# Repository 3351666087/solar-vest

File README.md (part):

<div align="center">

# Solar Vest

**A self-powered, solar-harvesting wearable for ECG research**<br>
**一件为心电研究而做的太阳能自供电可穿戴背心**

**[English](#english) | [中文](#中文)**

</div>

---

## English

### What it is

Solar Vest is a research platform that answers one question:

> **Can a body-worn 6 V / 6 W solar panel keep a Bluetooth ECG acquisition unit running, and does solar powering change the ECG signal compared with an identical battery-powered control recorded on the same subject at the same time?**

A rigid 6 V / 6 W panel rides on the back of a vest. It charges a 1S Li-ion cell through **PMB-H**, an MPPT charger and power-monitor board of our own design. The battery feeds **BITalino B** (the device under test) through **LIB**, an ideal-diode hold-up board with supercapacitors. **BITalino C** records ECG from mirror-symmetric electrodes on its own battery as the control, and **BITalino A** (HeartBIT) adds ear-lobe PPG. Six INA226 monitors log every energy path, and a XIAO nRF52840 streams the telemetry over BLE to a gateway and on to a remote web console.

The energy budget (see [docs/architecture-v3.md](docs/architecture-v3.md)) says continuous acquisition is only fully self-powered on good days; on a typical day the panel extends runtime by about 76 %, and duty-cycled measurement reaches energy balance.

### System architecture

```mermaid
flowchart LR
    PV["6 V / 6 W solar panel"] --> PMB
    REF["REF1 / REF2 reference cells"] --> PMB

    subgraph PMB["PMB-H (back pod)"]
        direction TB
        CHG["CN3791 MPPT charger<br/>night back-feed cut-off"]
        INA["6 x INA226<br/>PV hi/lo, BAT, LOAD, REF1, REF2"]
        MCU["XIAO nRF52840 Sense<br/>firmware v2"]
        INA -- "I2C" --> MCU
    end

    CHG <--> BAT["1S Li-ion 2500 mAh"]
    PMB -- "VLOAD (LOAD_EN)" --> LIB["LIB (chest pod)<br/>LM66100 ideal diode<br/>+ 2 x 10 F supercaps"]
    LIB --> B["BITalino B<br/>Core BLE, ECG (DUT)"]
    C["BITalino C<br/>Board Kit BLE, ECG<br/>own battery (control)"]
    A["BITalino A<br/>HeartBIT, ear-lobe PPG"]

    MCU -- "BLE telemetry / commands" --> GW["Gateway<br/>Mac (bleak) | ESP32 (MicroPython) | browser relay"]
    GW -- "HTTPS /api/ingest" --> SRV["Console server<br/>console.example.org"]
    SRV --> UI["Web console"]
    B -. "BLE ECG" .-> PHONE["Phone / Mac recording"]
    C -. "BLE ECG" .-> PHONE
    A -. "Classic BT PPG" .-> PHONE
```

### Hardware

| Part | What it is | Where |
|---|---|---|
| **PMB-H** (back pod) | CN3791 MPPT charger (set point 5.93 V), night back-feed cut-off, 6 × INA226 (panel high / indoor range, battery, load, two reference cells), NTC, XIAO nRF52840 Sense logger | [`hardware/pcb/pmbh/`](hardware/pcb/pmbh/) |
| **LIB** (chest pod) | Hold-up board: feeds BITalino Core B through an LM66100 ideal diode; 2 × 10 F supercaps take over if the supply drops | [`hardware/pcb/libb/`](hardware/pcb/libb/) |
| Fabrication outputs | KiCad 10 projects (generated from SKiDL), schematics PDF, Gerbers, JLCPCB BOM + CPL (`*_v3.xlsx` are the ordered files), 3D models, final placement images, rotation audit | [`hardware/pcb/`](hardware/pcb/) |
| Enclosures | 18 printable parts (STEP / STL / 3MF): back pod, chest pod, C case, ear clip, six panel shoes (18–52 mm air gap), REF holders, bench stand, webbing hook | [`hardware/enclosures/`](hardware/enclosures/) (read `README_print-list.txt`) |
| Vest patterns | Shell, lining and accessory patterns: DXF, 1:1 plotter PDF, A4 tiles, body-fitted placement data | [`hardware/vest/`](hardware/vest/) |
| Wiring | 20-wire harness specified pin-to-pin with routed lengths: table (md / csv), system diagram (svg), interactive guide | [`hardware/wiring/`](hardware/wiring/) |
| BITalino A / B / C | A: HeartBIT (Core BT) + ear-lobe PPG · B: Core BLE, solar-powered DUT · C: Board Kit BLE on its own battery (control) | [`docs/bom-and-system-overview.md`](docs/bom-and-system-overview.md) |

### Software

| Component | What it is | Where |
|---|---|---|
| Firmware | Arduino sketch for the XIAO nRF52840: INA226 sampling, MPPT / charge / load control, safety lockouts, BLE GATT telemetry and commands, settings persisted in flash | [`firmware/solarvest_pmb/`](firmware/solarvest_pmb/) |
| Bring-up sketch | Serial-console bench test for PMB-H (toggle every control pin, read every INA226) | [`firmware/pmbh_bringup/`](firmware/pmbh_bringup/), [`tools/serial_bridge.py`](tools/serial_bridge.py) |
| Console server | Python 3.12, standard library only; SQLite storage, session login, device-token ingest, command queue; single-file HTML console with Web Bluetooth relay | [`software/server/`](software/server/) |
| Mac gateway | Python + `bleak`; BLE central → HTTPS, offline buffer, runs unattended under `caffeinate` | [`software/gateway-mac/`](software/gateway-mac/) |
| ESP32 gateway | MicroPython 1.28 port of the same gateway (uses `aioble`) | [`software/gateway-esp32/`](software/gateway-esp32/) |
| Protocol | Interface spec (GATT layout, HTTP API, console UI) and shared decode test vectors | [`software/SPEC.md`](software/SPEC.md), [`software/protocol/vectors.json`](software/protocol/vectors.json) |
| CAD / EDA generators | build123d enclosures, SKiDL / pcbnew board scripts, JLCPCB rotation check, vest patterns, harness, fit checks, ngspice testbenches | [`tools/cad/`](tools/cad/) |

### Repository map

```text
.
├── docs/          Architecture v3 (+ v1/v2 history), v3.1 change list, build & assembly guide,
│                  BOM cross-reference, retrospective, tailoring survey, renders
├── hardware/      PCB projects and fab files, printable enclosures, vest patterns, wiring
├── firmware/      XIAO nRF52840 firmware, bench bring-up sketch, packing check
├── software/      Console server, Mac and ESP32 gateways, protocol spec and test vectors
├── simulation/    ngspice report and figures (MPPT stability, night back-feed, hold-up)
├── explorer/      Interactive 3D explorer (open index.html, works offline)
├── viewer/        Earlier glTF viewer of the full assembly (incl. a body-fitted variant)
├── modeling/      Component models: BITalino Core, panel, supercap, HeartBIT kit, viewer
├── body/          Body reconstruction used to fit the vest (owner's data, published with consent)
├── research/      Toolchain survey and the parametric samples that validated it
├── tools/         CAD/EDA/simulation generators, explorer source, serial bridge
├── pdf/           Pipeline that typesets the architecture documents to PDF (fonts not included)
└── THIRD_PARTY_NOTICES.md
```

Start with [docs/build-and-assembly-guide.md](docs/build-and-assembly-guide.md).

### Quick start

<details>
<summary><b>See the design</b></summary>

Open [`explorer/index.html`](explorer/index.html) in Chrome, Edge or Safari (works offline). Press `P` for the guided tour, `X` for X-ray and `E` to explode. The wiring guide is [`hardware/wiring/wiring-guide.html`](hardware/wiring/wiring-guide.html).

</details>

<details>
<summary><b>Build and flash the firmware</b></summary>

Core `Seeeduino:nrf52` 1.1.13 (Adafruit Bluefruit based). No external libraries are needed.

```bash
arduino-cli config add board_manager.additional_urls \
  https://files.seeedstudio.com/arduino/package_seeeduino_boards_index.json
arduino-cli core update-index
arduino-cli core install Seeeduino:nrf52@1.1.13

FQBN=Seeeduino:nrf52:xiaonRF52840Sense
arduino-cli compile --fqbn $FQBN firmware/solarvest_pmb
arduino-cli upload  --fqbn $FQBN -p /dev/cu.usbmodem101 firmware/solarvest_pmb

python3 firmware/pack_check.py          # firmware packing vs protocol vectors
```

For a first power-up use `firmware/pmbh_bringup` instead (serial 115200; `h` prints help).

</details>

<details>
<summary><b>Run the server tests and a local server</b></summary>

```bash
cd software/server
python3 test_server.py                  # end-to-end HTTP tests (stdlib unittest)
node test_decoder.mjs                   # console JS decoder vs vectors.json
python3 ../gateway-esp32/test_host.py   # ESP32 gateway logic on CPython

SV_CONSOLE_PASSWORD=change-me SV_DEVICE_TOKEN=dev-token SV_SESSION_SECRET=$(openssl rand -hex 32) \
SV_DB=./solarvest.db SV_COOKIE_SECURE=0 PORT=8790 python3 server.py
# then open http://localhost:8790
```

</details>

<details>
<summary><b>Deploy (Docker behind Caddy)</b></summary>

[`software/deploy.sh`](software/deploy.sh) copies the server to a Docker host that already runs a Caddy edge container, builds the image and adds a site block. Everything is set through environment variables; the values below are placeholders.

```bash
# ~/.config/solarvest/server.env holds SV_CONSOLE_PASSWORD, SV_DEVICE_TOKEN, SV_SESSION_SECRET
SV_SSH_HOST=your-server SV_DOMAIN=console.example.org \
SV_DOCKER_NETWORK=web SV_EDGE_CONTAINER=caddy ./software/deploy.sh
```

</details>

<details>
<summary><b>Run a gateway</b></summary>

**Mac** (unattended, sleep prevented):

```bash
mkdir -p ~/.config/solarvest
printf 'SV_URL=https://console.example.org\nSV_DEVICE_TOKEN=...\n' > ~/.config/solarvest/gateway.env
./software/gateway-mac/run.sh            # creates .venv, installs bleak, runs gateway.py
python3 software/gateway-mac/gateway.py --selftest   # decoder check, exit 0/1
python3 software/gateway-mac/gateway.py --dry-run    # replay vectors without Bluetooth
```

**Browser relay**: log in to the console in Chrome / Edge on Android or a Mac and use the panel *Use this device as the gateway* (Web Bluetooth; the screen must stay on; not available in Safari / iOS).

**ESP32**: `software/gateway-esp32/push.sh [port]` uploads `aioble`, `main.py` and a `config.json` built from `~/.config/solarvest/gateway.env` and `~/.config/solarvest/wifi.json`.

</details>

<details>
<summary><b>Rebuild the CAD, PCBs and explorer</b></summary>

Everything is generated by code; there is no GUI CAD.

| What | How |
|---|---|
| Explorer | `cd tools/cad/SolarVest_Explorer_src && npm install && npm run build` (three 0.160, three-mesh-bvh 0.8, esbuild) |
| Enclosures | Python 3.12 + `build123d trimesh manifold3d scipy shapely`: `tools/cad/enclosures.py` (the panel shoes also need the body model, which is not included) |
| Fit check | `python tools/cad/check_fit.py <parts dir> <data dir>`: interference and free travel of every board and battery |
| PCBs | KiCad 10 + SKiDL: `tools/cad/pmbh.py`, `libb.py`, then `place_*.py`, `fab.py` (Gerbers, BOM, CPL), `jlc_rotcheck.py` (pad-matched placement rotations) |
| Simulation | ngspice through KiCad's bundled libngspice: `tools/cad/simulation/` |

Some scripts expect tool locations from the original workstation (KiCad app path, scratch directories); adapt them as needed.

</details>

### Current status

**Bench bring-up done (2026-10-28):**

- [x] Both PCBs manufactured and assembled by JLCPCB, powered up on the bench
- [x] All six INA226 monitors answer and read plausible values
- [x] BITalino Core B powered through LIB and streaming ECG over BLE
- [x] Remote console live, with a full command round-trip (console → server → gateway → XIAO → ack)
- [x] Firmware v2: autoload (load on at ≥ 3.7 V, persisted in flash) and gateway keepalive

**Next:**

- [ ] Sunny-day charging validation outdoors (MPPT operating point, energy balance)
- [ ] ECG comparison: B (solar) vs C (battery control), same subject, same time
- [ ] Sew the vest and move from bench to body

### Safety

> [!WARNING]
> BITalino is a research device, **not a medical device**.

- **Electrodes and mains**: while electrodes are on the body, never connect USB or any mains-powered equipment to any unit. Data goes over Bluetooth only; B has no USB port in the chest pod and draws power only from the vest battery. Charge A and C only after the vest is taken off.
- **Li-ion**: use a protected cell; the firmware limits charging to 0–45 °C via the battery NTC and locks out the load on low voltage. The back pod sits outside the panel's shadow. Check polarity (red wire to J2 "+") before connecting.
- **Heat**: on a sunny day the back of the panel can reach 60–70 °C; keep the air gap and stop extended wear if the vest surface under the panel exceeds 40 °C.

Details: [docs/bom-and-system-overview.md](docs/bom-and-system-overview.md).

### Credits and third-party content

- See [THIRD_PARTY_NOTICES.md](THIRD_PARTY_NOTICES.md) for every item and its license.
- **PLUX / BITalino**: dimensions are cited from PLUX's manuals and data sheets; PLUX documentation, photos and vendor CAD are not redistributed.
- **Thingiverse models** by BITalinoWorld / BEE Very Creative: CC BY 4.0 (Plugged Casing, ECG Sensor Housing) and CC0 1.0 (PulseSensor Housing), in `modeling/`.
- **micropython-lib `aioble`** (MIT, © 2021 Jim Mussared), vendored in `software/gateway-esp32/lib/aioble/`.
- three.js, three-mesh-bvh and the meshopt decoder (MIT) are bundled in the web viewers.

### Privacy

Personal identifiers (names, institution, e-mail addresses, local paths, third-party contacts) have been removed; the supervisor is referred to by role only. The body data in `body/` and `viewer/*_PRIVATE*.glb` belongs to the project owner and is published with their consent.

### License

No license has been chosen yet, so all rights are reserved by the author. Third-party parts keep their own licenses (see the notices).

<p align="right"><a href="#solar-vest">Back to top</a></p>

---

## 中文

### 这是什么

Solar Vest 是一个研究平台，要回答的问题只有一个：

> **一块穿在身上的 6 V / 6 W 太阳能板，能不能让蓝牙心电采集单元持续工作？和同一个人、同一时间、用电池供电的同款对照组相比，太阳能供电会不会影响心电信号？**

背心后背装一块 6 V / 6 W 硬质太阳能板，经自研的 MPPT 充电与功率监测板 **PMB-H** 给单节锂电充电。电池通过 **LIB**（理想二极管 + 超级电容的掉电保持板）给 **BITalino B**（被测设备）供电；**BITalino C** 用自己的电池、在镜像对称的电极位置同步采集心电作为对照；**BITalino A**（HeartBIT）另外采集耳垂 PPG。6 路 INA226 记录每一条能量路径，XIAO nRF52840 把遥测数据经 BLE 发给网关，再上传到远程网页控制台。

按能量预算（见 [docs/architecture-v3.md](docs/architecture-v3.md)）：连续采集只有在好天气下才能完全自供电；典型日子里太阳能能把续航延长约 76%，改为间歇测量则可以做到能量收支平衡。

### 系统架构

```mermaid
flowchart LR
    PV["6 V / 6 W 太阳能板"] --> PMB
    REF["REF1 / REF2 参考电池片"] --> PMB

    subgraph PMB["PMB-H（背部仓）"]
        direction TB
        CHG["CN3791 MPPT 充电<br/>夜间防倒灌"]
        INA["6 × INA226<br/>PV 高/低量程、BAT、LOAD、REF1、REF2"]
        MCU["XIAO nRF52840 Sense<br/>固件 v2"]
        INA -- "I2C" --> MCU
    end

    CHG <--> BAT["单节锂电 2500 mAh"]
    PMB -- "VLOAD（LOAD_EN）" --> LIB["LIB（胸前仓）<br/>LM66100 理想二极管<br/>+ 2 × 10 F 超级电容"]
    LIB --> B["BITalino B<br/>Core BLE，心电（被测）"]
    C["BITalino C<br/>Board Kit BLE，心电<br/>自带电池（对照）"]
    A["BITalino A<br/>HeartBIT，耳垂 PPG"]

    MCU -- "BLE 遥测 / 指令" --> GW["网关<br/>Mac（bleak）| ESP32（MicroPython）| 浏览器中继"]
    GW -- "HTTPS /api/ingest" --> SRV["控制台服务器<br/>console.example.org"]
    SRV --> UI["网页控制台"]
    B -. "BLE 心电" .-> PHONE["手机 / Mac 记录"]
    C -. "BLE 心电" .-> PHONE
    A -. "经典蓝牙 PPG" .-> PHONE
```

### 硬件

| 部分 | 说明 | 位置 |
|---|---|---|
| **PMB-H**（背部仓） | CN3791 MPPT 充电（设定点 5.93 V）、夜间防倒灌、6 × INA226（太阳能板高量程/室内量程、电池、负载、两块参考电池片）、NTC、XIAO nRF52840 Sense 记录仪 | [`hardware/pcb/pmbh/`](hardware/pcb/pmbh/) |
| **LIB**（胸前仓） | 掉电保持板：经 LM66100 理想二极管给 BITalino Core B 供电，供电跌落时由 2 × 10 F 超级电容接管 | [`hardware/pcb/libb/`](hardware/pcb/libb/) |
| 生产文件 | KiCad 10 工程（由 SKiDL 生成）、原理图 PDF、Gerber、嘉立创 BOM + 坐标文件（`*_v3.xlsx` 为实际下单版本）、3D 模型、最终贴片图、旋转角核对 | [`hardware/pcb/`](hardware/pcb/) |
| 外壳 | 18 个打印件（STEP / STL / 3MF）：背部仓、胸前仓、C 外壳、耳夹、6 个太阳能板支脚（留 18–52 mm 空气层）、参考电池片支架、桌面支架、织带挂钩 | [`hardware/enclosures/`](hardware/enclosures/)（先看 `README_print-list.txt`） |
| 背心版型 | 面料、里料、配件版型：DXF、1:1 绘图仪 PDF、A4 拼贴、贴合身体的布局数据 | [`hardware/vest/`](hardware/vest/) |
| 接线 | 20 根线的线束，逐针定义并给出走线长度：接线表（md / csv）、系统接线图（svg）、交互式指南 | [`hardware/wiring/`](hardware/wiring/) |
| BITalino A / B / C | A：HeartBIT（Core BT）+ 耳垂 PPG · B：Core BLE，太阳能供电的被测设备 · C：Board Kit BLE，自带电池（对照） | [`docs/bom-and-system-overview.md`](docs/bom-and-system-overview.md) |

### 软件

| 组件 | 说明 | 位置 |
|---|---|---|
| 固件 | XIAO nRF52840 的 Arduino 程序：INA226 采样、MPPT / 充电 / 负载控制、安全锁定、BLE GATT 遥测与指令、设置存入 flash | [`firmware/solarvest_pmb/`](firmware/solarvest_pmb/) |
| 点亮测试程序 | PMB-H 桌面测试，走串口：逐个切换控制引脚、读取每颗 INA226 | [`firmware/pmbh_bringup/`](firmware/pmbh_bringup/)、[`tools/serial_bridge.py`](tools/serial_bridge.py) |
| 控制台服务器 | Python 3.12，只用标准库；SQLite 存储、登录会话、设备令牌上传、指令队列；单文件 HTML 控制台，自带 Web Bluetooth 中继 | [`software/server/`](software/server/) |
| Mac 网关 | Python + `bleak`；BLE 主机 → HTTPS，离线缓存，用 `caffeinate` 防休眠、无人值守运行 | [`software/gateway-mac/`](software/gateway-mac/) |
| ESP32 网关 | 同一网关的 MicroPython 1.28 移植版（基于 `aioble`） | [`software/gateway-esp32/`](software/gateway-esp32/) |
| 协议 | 接口规范（GATT 布局、HTTP API、控制台界面）和共用的解码测试向量 | [`software/SPEC.md`](software/SPEC.md)、[`software/protocol/vectors.json`](software/protocol/vectors.json) |
| CAD / EDA 生成脚本 | build123d 外壳、SKiDL / pcbnew 电路板脚本、嘉立创旋转角核对、背心版型、线束、装配干涉检查、ngspice 仿真 | [`tools/cad/`](tools/cad/) |

### 目录结构

```text
.
├── docs/          架构文档 v3（及 v1/v2 历史版本）、v3.1 变更清单、制造与装配指南、
│                  物料对照、项目回顾、裁缝调研、效果图
├── hardware/      PCB 工程与生产文件、可打印外壳、背心版型、接线
├── firmware/      XIAO nRF52840 固件、桌面点亮程序、打包校验
├── software/      控制台服务器、Mac 与 ESP32 网关、协议规范与测试向量
├── simulation/    ngspice 仿真报告与图（MPPT 稳定性、夜间倒灌、掉电保持）
├── explorer/      交互式 3D 浏览器（打开 index.html，可离线使用）
├── viewer/        早期的整机 glTF 查看器（含贴合人体的版本）
├── modeling/      元件建模：BITalino Core、太阳能板、超级电容、HeartBIT 套件、查看器
├── body/          用于背心贴合的人体还原（项目负责人本人数据，经本人同意公开）
├── research/      工具链调研及验证用的参数化样例
├── tools/         CAD/EDA/仿真生成脚本、3D 浏览器源码、串口桥
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
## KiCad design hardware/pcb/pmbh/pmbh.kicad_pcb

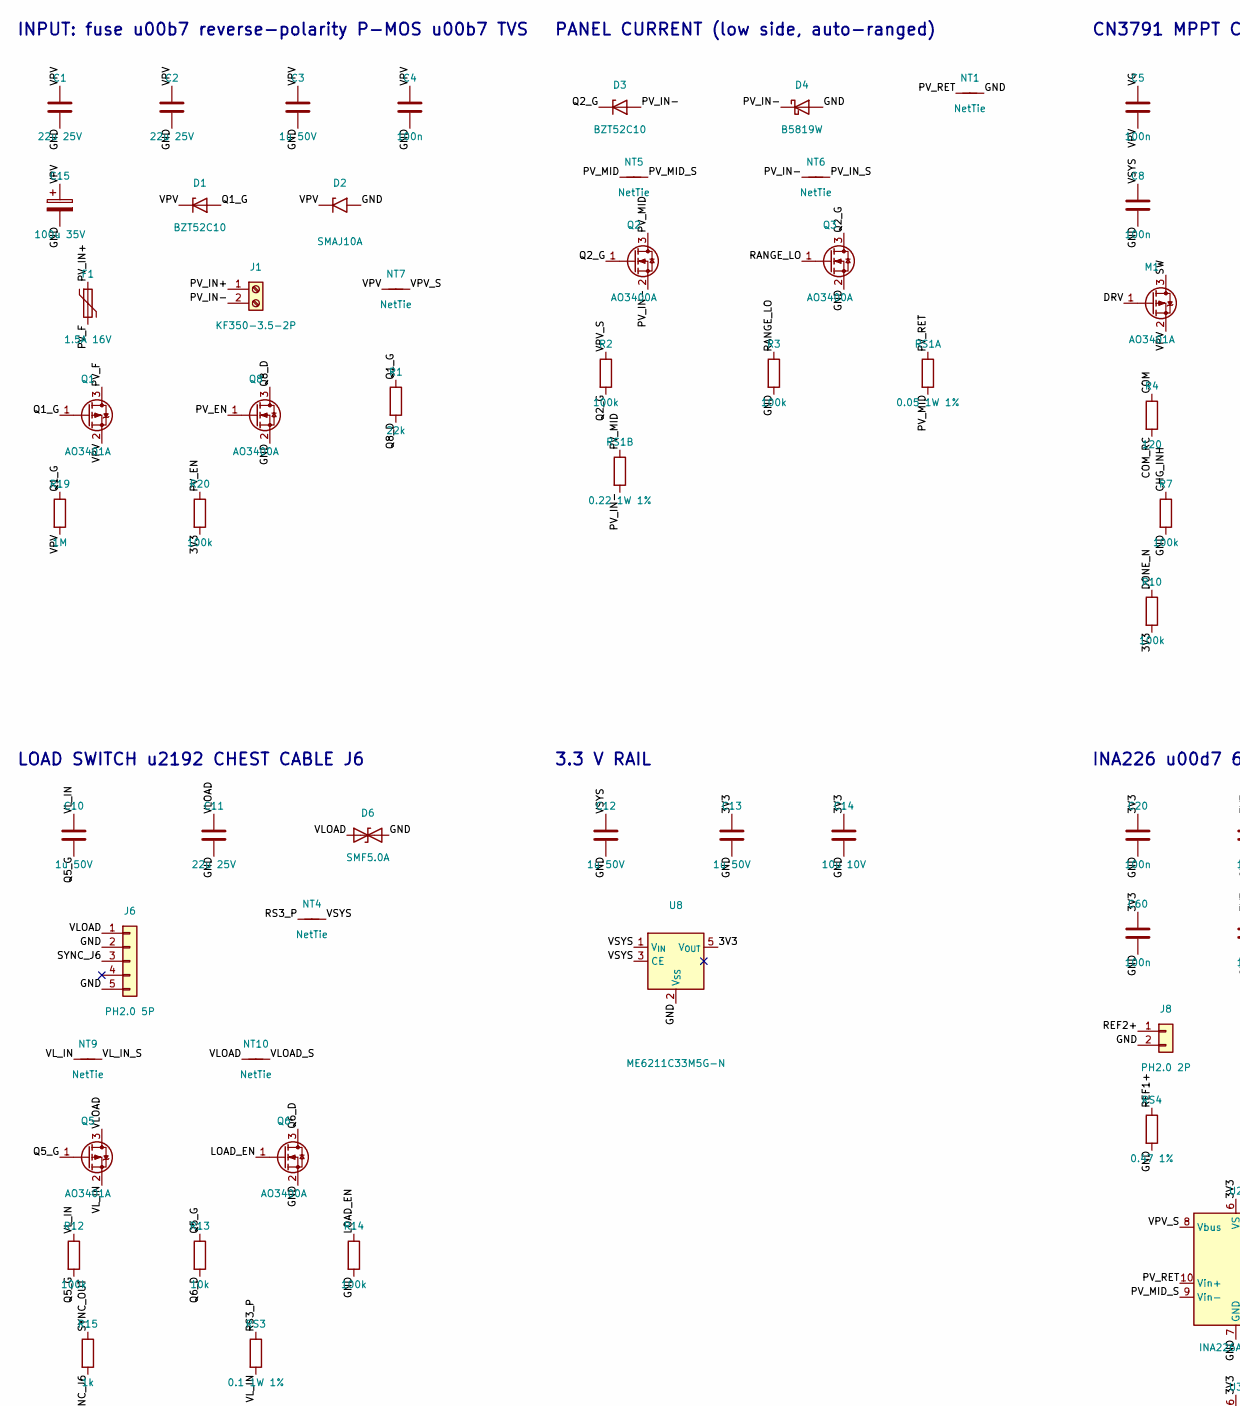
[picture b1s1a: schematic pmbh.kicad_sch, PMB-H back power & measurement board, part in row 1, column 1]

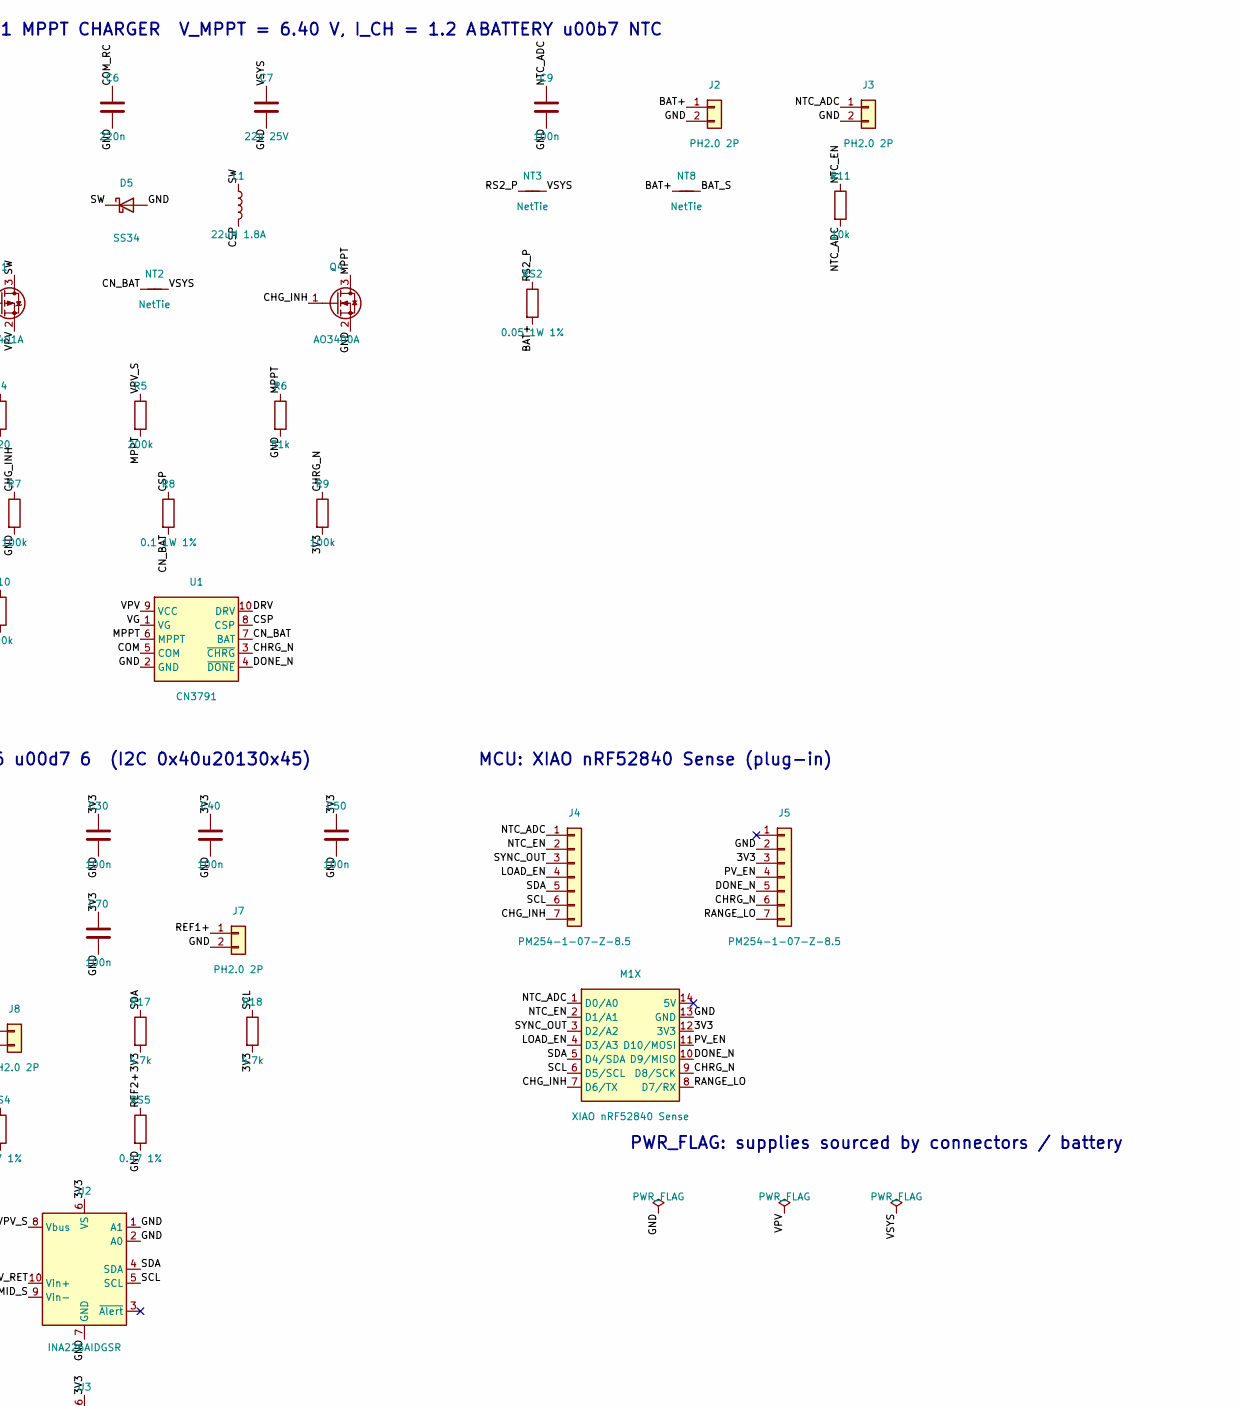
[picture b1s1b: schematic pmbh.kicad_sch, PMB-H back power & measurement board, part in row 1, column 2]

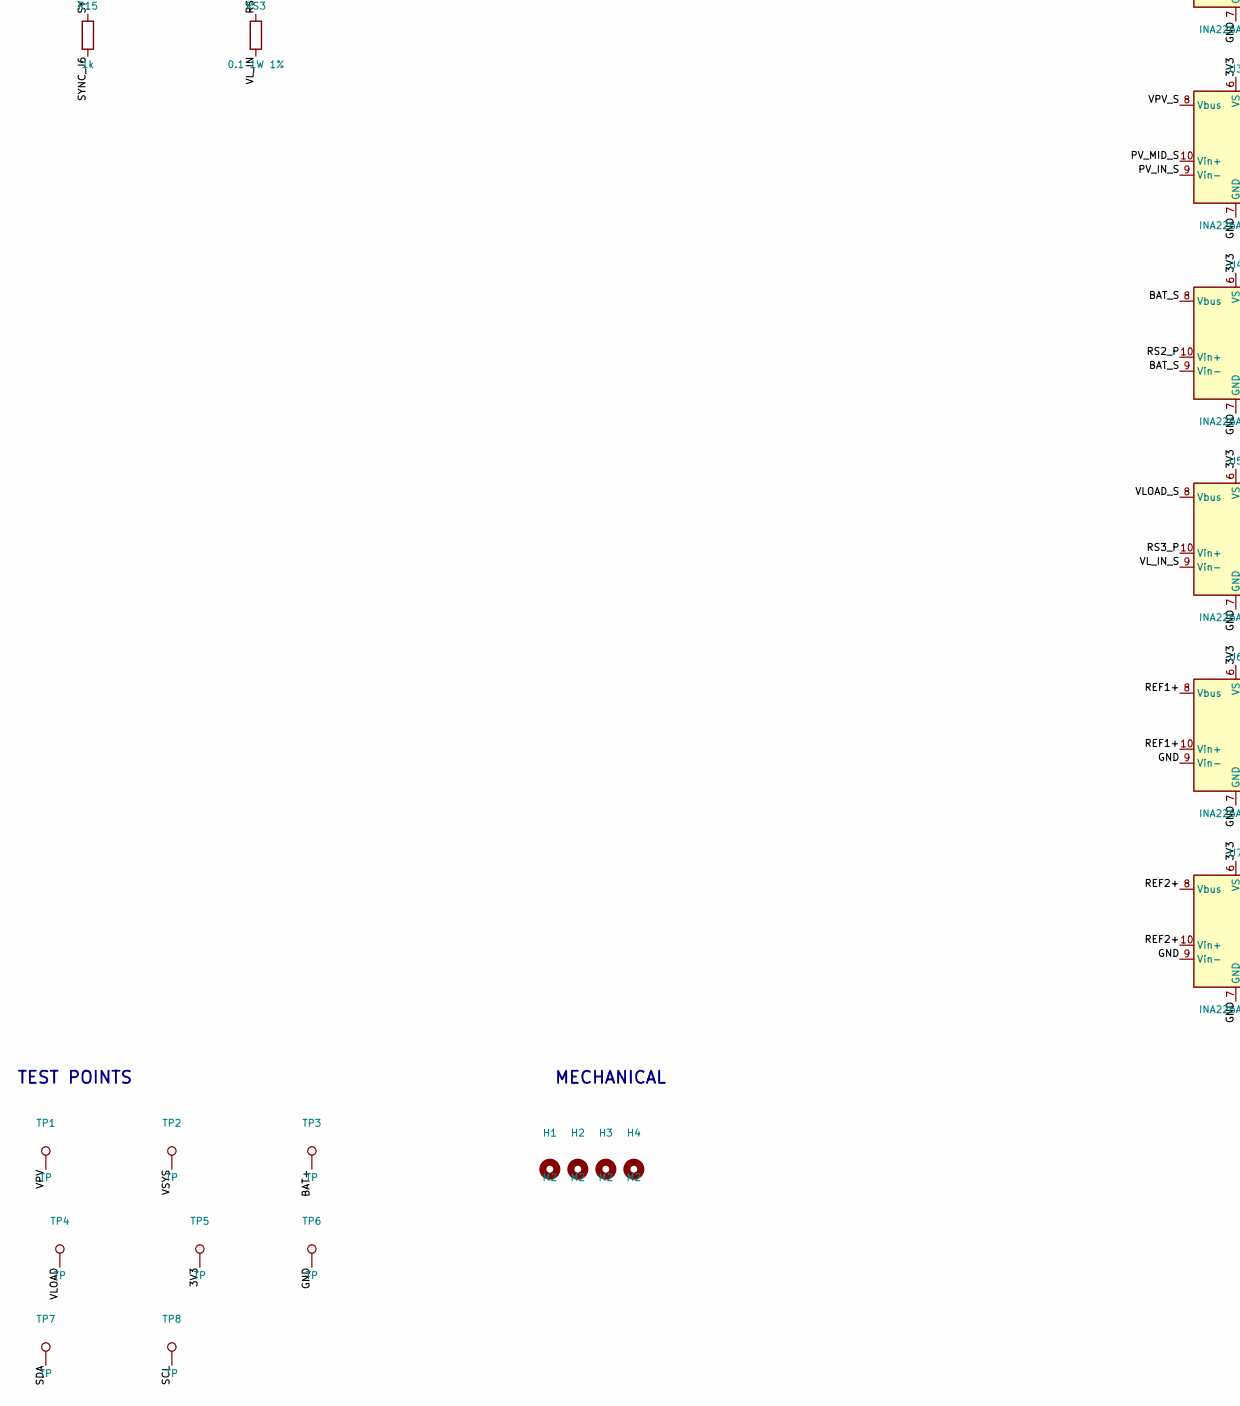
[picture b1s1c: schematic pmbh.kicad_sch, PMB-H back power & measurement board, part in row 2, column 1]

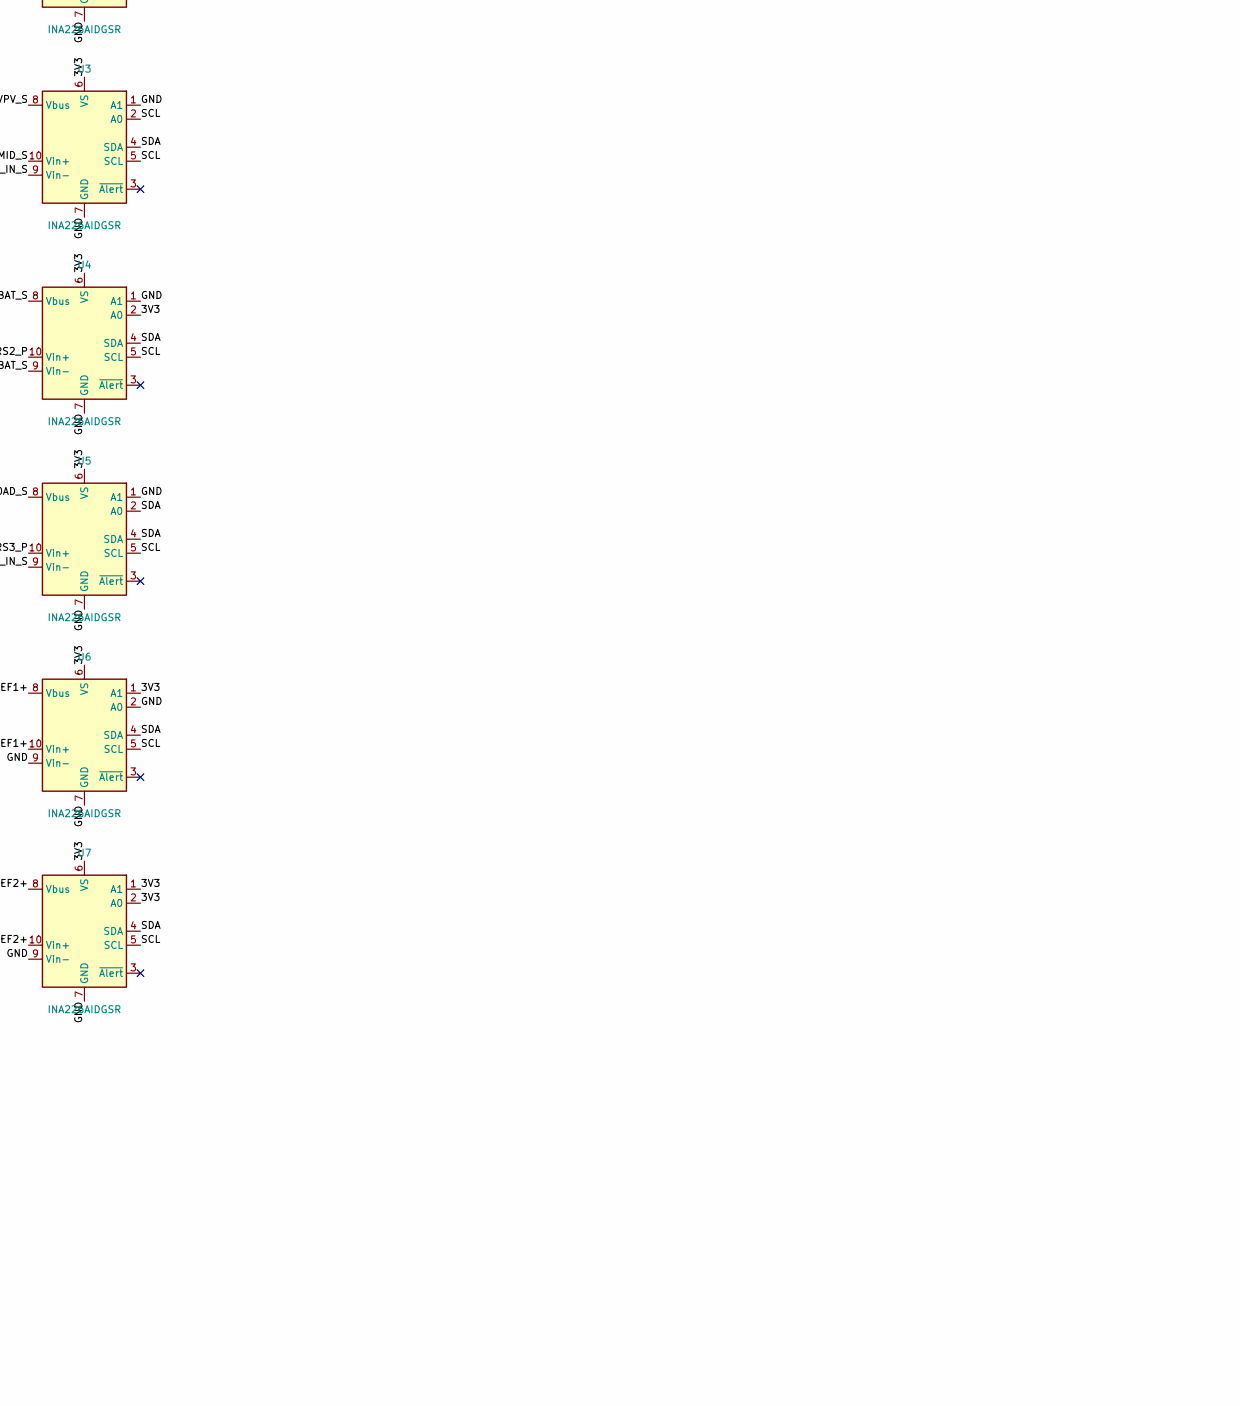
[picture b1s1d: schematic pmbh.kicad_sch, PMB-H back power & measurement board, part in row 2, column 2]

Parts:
C1, C2, C7, C11: 22u 25V; C_0805_2012Metric; LCSC C45783
C3, C10, C12, C13: 1u 50V; C_0603_1608Metric; LCSC C15849
C4, C5, C8, C9, C20, C30, C40, C50, C60, C70: 100n; C_0603_1608Metric; LCSC C14663
C6: 220n; C_0603_1608Metric; LCSC C21120
C14: 10u 10V; C_0603_1608Metric; LCSC C19702
C15: 100u 35V; CP_Elec_6.3x7.7; LCSC C2836437
D1, D3: BZT52C10; D_SOD-123; LCSC C173431
D2: SMAJ10A; D_SMA; LCSC C134939
D4: B5819W; D_SOD-123; LCSC C8598
D5: SS34; D_SMA; LCSC C8678
D6: SMF5.0A; D_SOD-123F; LCSC C193402
F1: 1.5A 16V; Fuse_1812_4532Metric; LCSC C883152
H1, H2, H3, H4: M2; MountingHole_2.2mm_M2
J1: KF350-3.5-2P; TerminalBlock_Phoenix_PT-1,5-2-3.5-H_1x02_P3.50mm_Horizontal; LCSC C474892
J2, J3, J7, J8: PH2.0 2P; JST_PH_S2B-PH-SM4-TB_1x02-1MP_P2.00mm_Horizontal; LCSC C295747
J4, J5: PM254-1-07-Z-8.5; PinSocket_1x07_P2.54mm_Vertical; LCSC C2897370
J6: PH2.0 5P; JST_PH_S5B-PH-SM4-TB_1x05-1MP_P2.00mm_Horizontal; LCSC C265104
L1: 22uH 1.8A; L_Sunlord_SWPA6045S; LCSC C83454
M1: AO3401A; SOT-23; LCSC C15127
M1X: XIAO nRF52840 Sense
NT1, NT2, NT3, NT4, NT5, NT6, NT7, NT8, NT9, NT10: NetTie; NetTie-2_SMD_Pad0.5mm
Q1, Q5: AO3401A; SOT-23; LCSC C15127
Q2, Q3, Q4, Q6, Q8: AO3400A; SOT-23; LCSC C20917
R1: 22k; R_0603_1608Metric; LCSC C31850
R2, R3, R7, R9, R10, R12, R14, R20: 100k; R_0603_1608Metric; LCSC C25803
R4: 120; R_0603_1608Metric; LCSC C22787
R5: 200k; R_0603_1608Metric; LCSC C25811
R6: 51k; R_0603_1608Metric; LCSC C23196
R8: 0.1 1W 1%; R_1206_3216Metric; LCSC C2903496
R11, R13: 10k; R_0603_1608Metric; LCSC C25804
R15: 1k; R_0603_1608Metric; LCSC C21190
R17, R18: 4.7k; R_0603_1608Metric; LCSC C23162
R19: 1M; R_0603_1608Metric; LCSC C22935
RS1A, RS2: 0.05 1W 1%; R_1206_3216Metric; LCSC C2904224
RS1B: 0.22 1W 1%; R_1206_3216Metric; LCSC C6627428
RS3: 0.1 1W 1%; R_1206_3216Metric; LCSC C2903496
RS4, RS5: 0.47 1%; R_1206_3216Metric; LCSC C28320
TP1, TP2, TP3, TP4, TP5, TP6, TP7, TP8: TP; TestPoint_Pad_D1.5mm
U1: CN3791; SSOP-10_3.9x4.9mm_P1.00mm; LCSC C154992
U2, U3, U4, U5, U6, U7: INA226AIDGSR; MSOP-10_3x3mm_P0.5mm; LCSC C49851
U8: ME6211C33M5G-N; SOT-23-5; LCSC C82942

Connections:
3V3: C13.1, C14.1, C20.1, C30.1, C40.1, C50.1, C60.1, C70.1, J5.3, M1X.12 (3V3), R9.2, R10.2, R17.2, R18.2, R20.2, TP5.1, U2.6 (VS), U3.6 (VS), U4.2 (A0), U4.6 (VS), U5.6 (VS), U6.1 (A1), U6.6 (VS), U7.1 (A1), U7.2 (A0), U7.6 (VS), U8.5 (V_{OUT})
BAT+: J2.1, NT8.1, RS2.2, TP3.1
BAT_S: NT8.2, U4.8 (Vbus), U4.9 (Vin-)
CHG_INH: J4.7, M1X.7 (D6/TX), Q4.1 (G), R7.1
CHRG_N: J5.6, M1X.9 (D8/SCK), R9.1, U1.3 (~CHRG)
CN_BAT: NT2.1, R8.2, U1.7 (BAT)
COM: R4.1, U1.5 (COM)
COM_RC: C6.1, R4.2
CSP: L1.2, R8.1, U1.8 (CSP)
DONE_N: J5.5, M1X.10 (D9/MISO), R10.1, U1.4 (~DONE)
DRV: M1.1 (G), U1.10 (DRV)
GND: C1.2, C2.2, C3.2, C4.2, C6.2, C7.2, C8.2, C9.2, C11.2, C12.2, C13.2, C14.2, C15.2, C20.2, C30.2, C40.2, C50.2, C60.2, C70.2, D2.2 (A2), D4.2 (A), D5.2 (A), D6.2 (A2), J2.2, J3.2, J5.2, J6.2, J6.5, J7.2, J8.2, M1X.13 (GND), NT1.2, Q3.2 (S), Q4.2 (S), Q6.2 (S), Q8.2 (S), R3.2, R6.2, R7.2, R14.2, RS4.2, RS5.2, TP6.1, U1.2 (GND), U2.1 (A1), U2.2 (A0), U2.7 (GND), U3.1 (A1), U3.7 (GND), U4.1 (A1), U4.7 (GND), U5.1 (A1), U5.7 (GND), U6.2 (A0), U6.7 (GND), U6.9 (Vin-), U7.7 (GND), U7.9 (Vin-), U8.2 (V_{SS})
LOAD_EN: J4.4, M1X.4 (D3/A3), Q6.1 (G), R14.1
MPPT: Q4.3 (D), R5.2, R6.1, U1.6 (MPPT)
NTC_ADC: C9.1, J3.1, J4.1, M1X.1 (D0/A0), R11.2
NTC_EN: J4.2, M1X.2 (D1/A1), R11.1
PV_EN: J5.4, M1X.11 (D10/MOSI), Q8.1 (G), R20.1
PV_F: F1.2, Q1.3 (D)
PV_IN+: F1.1, J1.1
PV_IN-: D3.2 (A), D4.1 (K), J1.2, NT6.1, Q2.2 (S), RS1B.2
PV_IN_S: NT6.2, U3.9 (Vin-)
PV_MID: NT5.1, Q2.3 (D), RS1A.2, RS1B.1
PV_MID_S: NT5.2, U2.9 (Vin-), U3.10 (Vin+)
PV_RET: NT1.1, RS1A.1, U2.10 (Vin+)
Q1_G: D1.2 (A), Q1.1 (G), R1.1, R19.1
Q2_G: D3.1 (K), Q2.1 (G), Q3.3 (D), R2.2
Q5_G: C10.2, Q5.1 (G), R12.2, R13.1
Q6_D: Q6.3 (D), R13.2
Q8_D: Q8.3 (D), R1.2
RANGE_LO: J5.7, M1X.8 (D7/RX), Q3.1 (G), R3.1
REF1+: J7.1, RS4.1, U6.8 (Vbus), U6.10 (Vin+)
REF2+: J8.1, RS5.1, U7.8 (Vbus), U7.10 (Vin+)
RS2_P: NT3.1, RS2.1, U4.10 (Vin+)
RS3_P: NT4.1, RS3.1, U5.10 (Vin+)
SCL: J4.6, M1X.6 (D5/SCL), R18.1, TP8.1, U2.5 (SCL), U3.2 (A0), U3.5 (SCL), U4.5 (SCL), U5.5 (SCL), U6.5 (SCL), U7.5 (SCL)
SDA: J4.5, M1X.5 (D4/SDA), R17.1, TP7.1, U2.4 (SDA), U3.4 (SDA), U4.4 (SDA), U5.2 (A0), U5.4 (SDA), U6.4 (SDA), U7.4 (SDA)
SW: D5.1 (K), L1.1, M1.3 (D)
SYNC_J6: J6.3, R15.2
SYNC_OUT: J4.3, M1X.3 (D2/A2), R15.1
VG: C5.1, U1.1 (VG)
VLOAD: C11.1, D6.1 (A1), J6.1, NT10.1, Q5.3 (D), TP4.1
VLOAD_S: NT10.2, U5.8 (Vbus)
VL_IN: C10.1, NT9.1, Q5.2 (S), R12.1, RS3.2
VL_IN_S: NT9.2, U5.9 (Vin-)
VPV: C1.1, C2.1, C3.1, C4.1, C5.2, C15.1, D1.1 (K), D2.1 (A1), M1.2 (S), NT7.1, Q1.2 (S), R19.2, TP1.1, U1.9 (VCC)
VPV_S: NT7.2, R2.1, R5.1, U2.8 (Vbus), U3.8 (Vbus)
VSYS: C7.1, C8.1, C12.1, NT2.2, NT3.2, NT4.2, TP2.1, U8.1 (V_{IN}), U8.3 (CE)

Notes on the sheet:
INPUT: fuse u00b7 reverse-polarity P-MOS u00b7 TVS
PANEL CURRENT (low side, auto-ranged)
CN3791 MPPT CHARGER V_MPPT = 6.40 V, I_CH = 1.2 A
BATTERY u00b7 NTC
LOAD SWITCH u2192 CHEST CABLE J6
3.3 V RAIL
INA226 u00d7 6 (I2C 0x40u20130x45)
MCU: XIAO nRF52840 Sense (plug-in)
TEST POINTS
MECHANICAL
PWR_FLAG: supplies sourced by connectors / battery

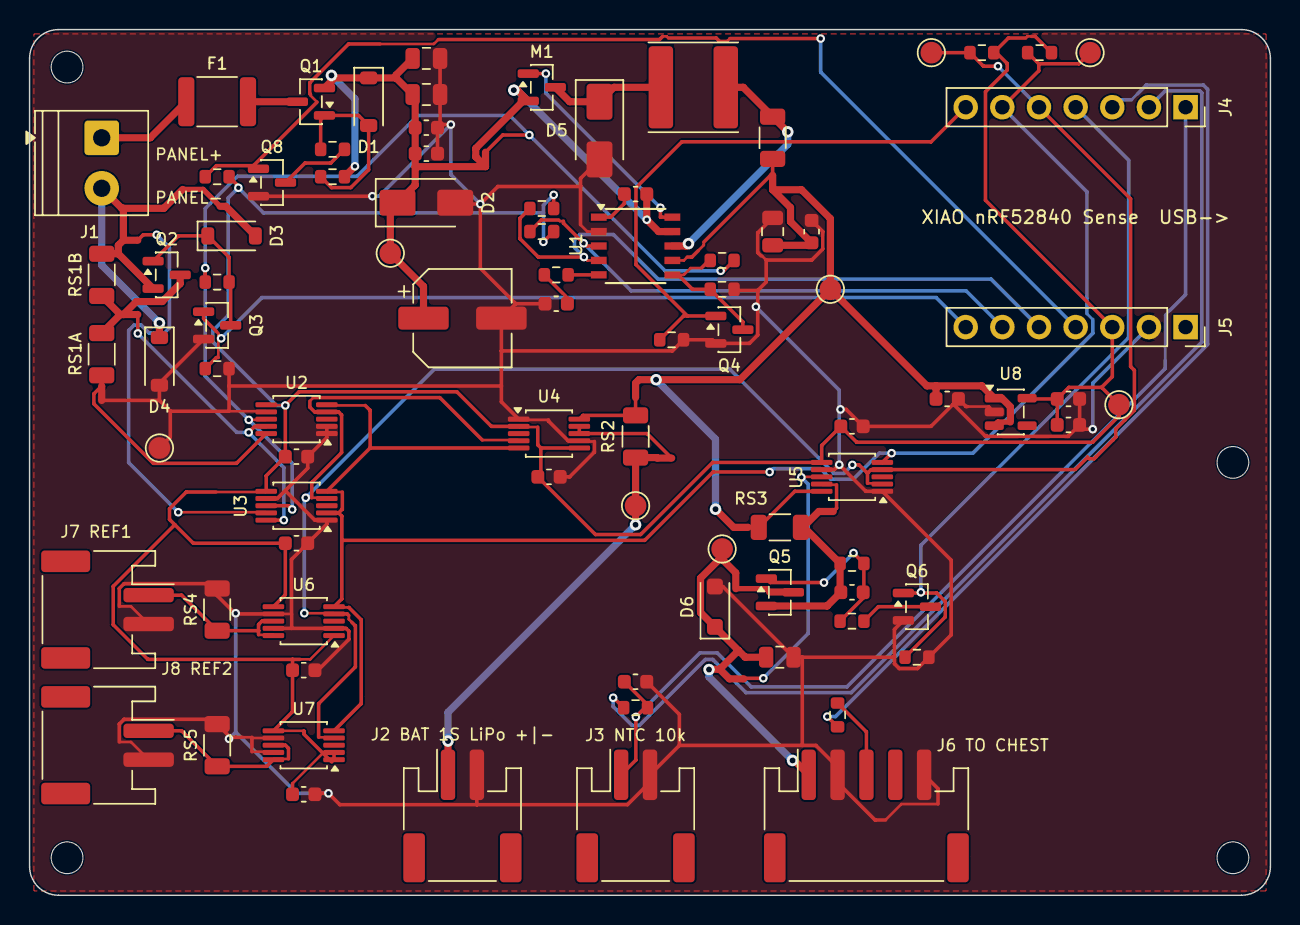
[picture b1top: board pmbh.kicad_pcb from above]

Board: 2 copper layers, 86.0 x 60.0 mm, 100 parts (0 on the bottom side), 47 nets.

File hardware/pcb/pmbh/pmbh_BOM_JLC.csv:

Comment,Designator,Footprint,LCSC Part #,Qty,JLC library
22u 25V,"C1,C2,C7,C11",C_0805_2012Metric,C45783,4,Basic
1u 50V,"C3,C10,C12,C13",C_0603_1608Metric,C15849,4,Basic
100n,"C4,C5,C8,C9,C20,C30,C40,C50,C60,C70",C_0603_1608Metric,C14663,10,Basic
220n,C6,C_0603_1608Metric,C21120,1,Basic
10u 10V,C14,C_0603_1608Metric,C19702,1,Basic
100u 35V,C15,CP_Elec_6.3x7.7,C2836437,1,Extended
BZT52C10,"D1,D3",D_SOD-123,C173431,2,Extended
SMAJ10A,D2,D_SMA,C134939,1,Extended
B5819W,D4,D_SOD-123,C8598,1,Basic
SS34,D5,D_SMA,C8678,1,Basic
SMF5.0A,D6,D_SOD-123F,C193402,1,Extended
1.5A 16V,F1,Fuse_1812_4532Metric,C883152,1,Extended
KF350-3.5-2P,J1,"TerminalBlock_Phoenix_PT-1,5-2-3.5-H_1x02_P3.50mm_Horizontal",C474892,1,Extended
PH2.0 2P,"J2,J3,J7,J8",JST_PH_S2B-PH-SM4-TB_1x02-1MP_P2.00mm_Horizontal,C295747,4,Extended
PM254-1-07-Z-8.5,"J4,J5",PinSocket_1x07_P2.54mm_Vertical,C2897370,2,Extended
PH2.0 5P,J6,JST_PH_S5B-PH-SM4-TB_1x05-1MP_P2.00mm_Horizontal,C265104,1,Extended
22uH 1.8A,L1,L_Sunlord_SWPA6045S,C83454,1,Extended
AO3401A,"M1,Q1,Q5",SOT-23,C15127,3,Basic
AO3400A,"Q2,Q3,Q4,Q6,Q8",SOT-23,C20917,5,Basic
22k,R1,R_0603_1608Metric,C31850,1,Basic
100k,"R2,R3,R7,R9,R10,R12,R14,R20",R_0603_1608Metric,C25803,8,Basic
120,R4,R_0603_1608Metric,C22787,1,Basic
200k,R5,R_0603_1608Metric,C25811,1,Basic
51k,R6,R_0603_1608Metric,C23196,1,Basic
0.1 1W 1%,"R8,RS3",R_1206_3216Metric,C2903496,2,Extended
10k,"R11,R13",R_0603_1608Metric,C25804,2,Basic
1k,R15,R_0603_1608Metric,C21190,1,Basic
4.7k,"R17,R18",R_0603_1608Metric,C23162,2,Basic
1M,R19,R_0603_1608Metric,C22935,1,Basic
0.05 1W 1%,"RS2,RS1A",R_1206_3216Metric,C2904224,2,Extended
0.47 1%,"RS4,RS5",R_1206_3216Metric,C28320,2,Extended
0.22 1W 1%,RS1B,R_1206_3216Metric,C6627428,1,Extended
CN3791,U1,SSOP-10_3.9x4.9mm_P1.00mm,C154992,1,Extended
INA226AIDGSR,"U2,U3,U4,U5,U6,U7",MSOP-10_3x3mm_P0.5mm,C49851,6,Extended
ME6211C33M5G-N,U8,SOT-23-5,C82942,1,Extended

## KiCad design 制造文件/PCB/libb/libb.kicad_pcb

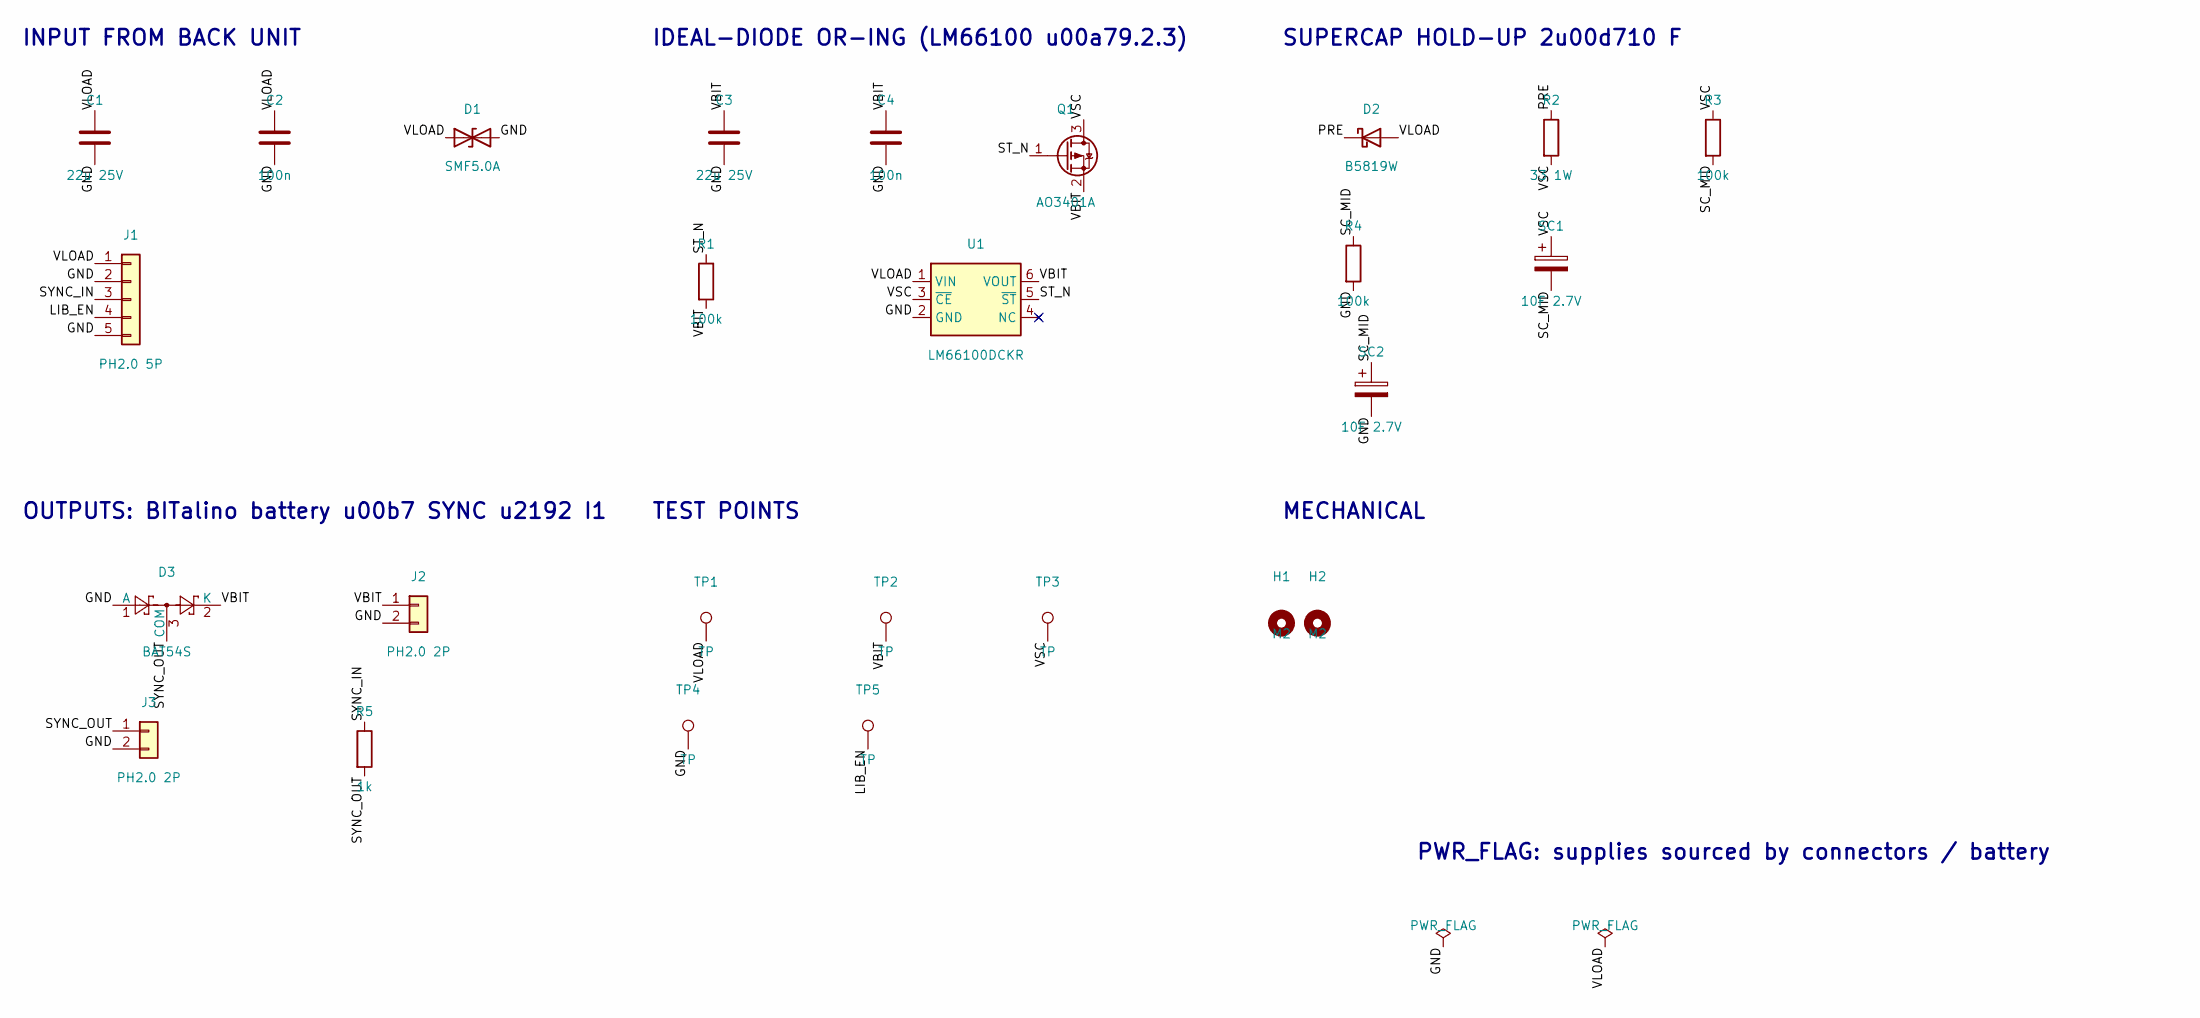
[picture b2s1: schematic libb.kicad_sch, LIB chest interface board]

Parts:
C1, C3: 22u 25V; C_0805_2012Metric; LCSC C45783
C2, C4: 100n; C_0603_1608Metric; LCSC C14663
D1: SMF5.0A; D_SOD-123F; LCSC C193402
D2: B5819W; D_SOD-123; LCSC C8598
D3: BAT54S; SOT-23; LCSC C47546
H1, H2: M2; MountingHole_2.2mm_M2
J1: PH2.0 5P; JST_PH_S5B-PH-SM4-TB_1x05-1MP_P2.00mm_Horizontal; LCSC C265104
J2, J3: PH2.0 2P; JST_PH_S2B-PH-SM4-TB_1x02-1MP_P2.00mm_Horizontal; LCSC C295747
Q1: AO3401A; SOT-23; LCSC C15127
R1, R3, R4: 100k; R_0603_1608Metric; LCSC C25803
R2: 33 1W; R_2512_6332Metric; LCSC C53728
R5: 1k; R_0603_1608Metric; LCSC C21190
SC1, SC2: 10F 2.7V; SuperCap_D10_L25_Flat_P5.00mm
TP1, TP2, TP3, TP4, TP5: TP; TestPoint_Pad_D1.5mm
U1: LM66100DCKR; SOT-363_SC-70-6; LCSC C2869734

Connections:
GND: C1.2, C2.2, C3.2, C4.2, D1.2 (A2), D3.1 (A), J1.2, J1.5, J2.2, J3.2, R4.2, SC2.2, TP4.1, U1.2 (GND)
LIB_EN: J1.4, TP5.1
PRE: D2.1 (K), R2.1
SC_MID: R3.2, R4.1, SC1.2, SC2.1
ST_N: Q1.1 (G), R1.1, U1.5 (~ST)
SYNC_IN: J1.3, R5.1
SYNC_OUT: D3.3 (COM), J3.1, R5.2
VBIT: C3.1, C4.1, D3.2 (K), J2.1, Q1.2 (S), R1.2, TP2.1, U1.6 (VOUT)
VLOAD: C1.1, C2.1, D1.1 (A1), D2.2 (A), J1.1, TP1.1, U1.1 (VIN)
VSC: Q1.3 (D), R2.2, R3.1, SC1.1, TP3.1, U1.3 (~CE)

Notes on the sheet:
INPUT FROM BACK UNIT
IDEAL-DIODE OR-ING (LM66100 u00a79.2.3)
SUPERCAP HOLD-UP 2u00d710 F
OUTPUTS: BITalino battery u00b7 SYNC u2192 I1
TEST POINTS
MECHANICAL
PWR_FLAG: supplies sourced by connectors / battery

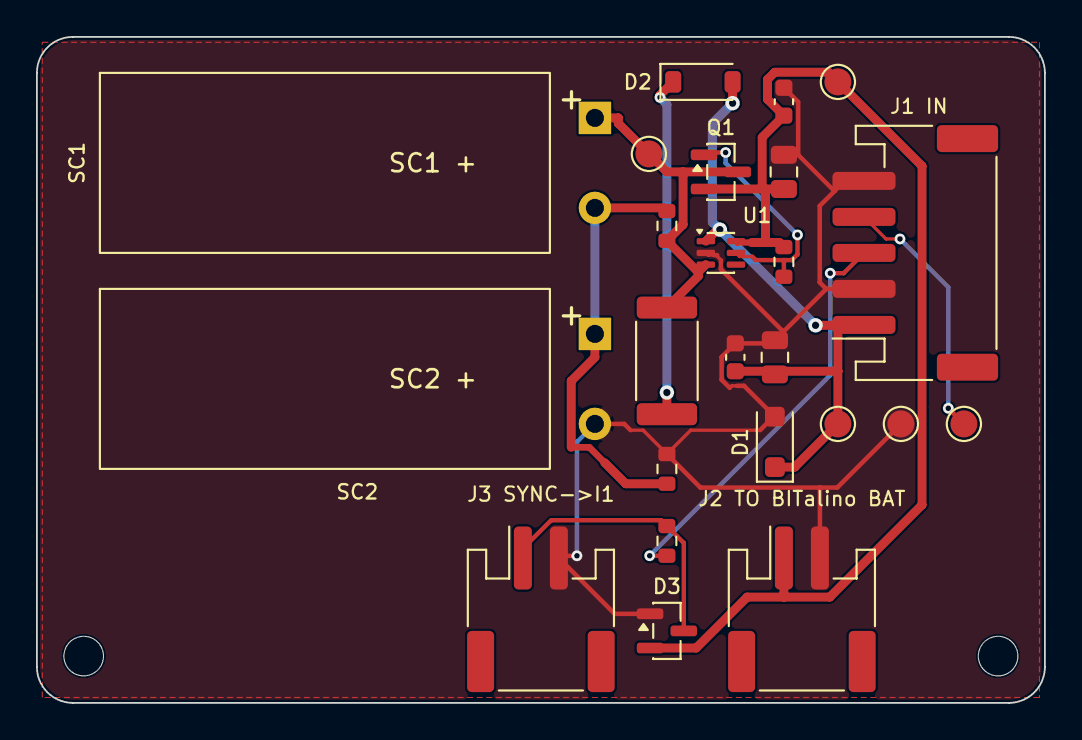
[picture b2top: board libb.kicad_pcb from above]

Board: 2 copper layers, 56.0 x 37.0 mm, 26 parts (0 on the bottom side), 10 nets.

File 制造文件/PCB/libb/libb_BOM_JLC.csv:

Comment,Designator,Footprint,LCSC Part #,Qty,JLC library
22u 25V,"C1,C3",C_0805_2012Metric,C45783,2,Basic
100n,"C2,C4",C_0603_1608Metric,C14663,2,Basic
SMF5.0A,D1,D_SOD-123F,C193402,1,Extended
B5819W,D2,D_SOD-123,C8598,1,Basic
BAT54S,D3,SOT-23,C47546,1,Extended
PH2.0 5P,J1,JST_PH_S5B-PH-SM4-TB_1x05-1MP_P2.00mm_Horizontal,C265104,1,Extended
PH2.0 2P,"J2,J3",JST_PH_S2B-PH-SM4-TB_1x02-1MP_P2.00mm_Horizontal,C295747,2,Extended
AO3401A,Q1,SOT-23,C15127,1,Basic
100k,"R1,R3,R4",R_0603_1608Metric,C25803,3,Basic
33 1W,R2,R_2512_6332Metric,C53728,1,Extended
1k,R5,R_0603_1608Metric,C21190,1,Basic
LM66100DCKR,U1,SOT-363_SC-70-6,C2869734,1,Extended

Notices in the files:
README.md:
- **Thingiverse 模型**（BITalinoWorld / BEE Very Creative）：CC BY 4.0（Plugged Casing、ECG Sensor Housing）和 CC0 1.0（PulseSensor Housing），位于 `modeling/`。
- **micropython-lib `aioble`**（MIT，© 2021 Jim Mussared），随附于 `software/gateway-esp32/lib/aioble/`。
